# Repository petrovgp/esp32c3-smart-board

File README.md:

# ESP32-C3 Smart Board

A compact, battery-powered ESP32-C3 development board designed in **KiCad 9**, integrating power management, motion sensing, and display support in a small form factor. Ideal for low-power IoT or wearable applications.

## 🏢 Sponsor of today's project - PCBWay!

A huge thank you to PCBWay for sponsoring this project!

PCBWay provided high-quality PCB fabrication and assembly support, helping bring the hardware from prototype to reality. Their fast turnaround times, excellent communication, and reliable manufacturing made a big difference in the development process.

If you're looking for PCB manufacturing, assembly, CNC, or 3D-printing services, check out PCBWay **[here!](https://www.pcbway.com)**

Production files for this project were created using PCBWay KiCAD plugin and they can be used in PCBWay PCB and PCBA services right away!

Thanks again to PCBWay for supporting open-source hardware projects!

## 📸 Board design

---

## 🧠 Features

### ⚡ Core
- **ESP32-C3** RISC-V microcontroller with Wi-Fi and BLE 5.0
- Compact **42 × 45 mm** PCB designed in KiCad 9
  - 4 layer stackup: L1 Signal | L2 Ground | L3 Ground | L4 Signal + Power
- Integrated **Inverted-F antenna** for stable wireless performance

### 🔋 Power System
- Operable from **Li-Ion / Li-Po battery** and **USB Type C**
- On-board **TP4056** linear charging IC
  - 250mA charging current configuration
- **DW01A + FS8205A** dual MOSFET battery protection circuit
- Power-sharing design — board can operate **while charging**
- **ME6211C** LDO regulator:
  - 500 mA max output current
  - 100 mV dropout at 100 mA

### 🧭 Sensors
- **MPU6050** 6-axis accelerometer and gyroscope  
  - Interrupt pin connected to ESP32-C3 for motion wake-up or gesture detection

### 🖥️ Display
- **GC9A01** round TFT display connector
  - 12-pin FPC interface for bare display module

### 🔌 Connectivity
- **USB Type-C** connector for power and programming
- Exposed UART pins for debugging

## 🧩 Production files
All design files were created in **KiCad 9** and production files have been exported with **PCBWay plugin** (available **[here](https://github.com/pcbway/PCBWay-Plug-in-for-Kicad.git)**):
- `schematics/` – full circuit schematics
- `kicad/` – KiCAD 9 project files
- `kicad/production/` – ready-to-manufacture files (GERBERs + BOM)

Adjustment of production files might be needed. Please check carefully before placing any manufacturing orders.

## 🧾 Revisions

| Revision | Manufactured | Notes | Available |
|-----------|------|-------|-----------|
| **v1.0** | Nov 2025 | Improper GC9A01 footprint (wrong pitch), improper PMOS power sharing footprint (SOT23-5 instead of SOT23-3), everything else verified as OK  | Not available on Github
| **v1.1** | _Not manufactured_ | Updated GC9A01 footprint pitch, updated PMOS power sharing footprint, layout and silkscreen changes | Tagged v1.1 on Github
| **v1.2** | Dec 2025 | Layout and silkscreen changes | Tagged v1.2 on Github
| **v1.3** | _Not manufactured_ | Footprint changes, battery section layout changes, rounded antenna trace, bottom layer 3.3V plane addition, layout and silkscreen changes| Tagged v1.3 on Github

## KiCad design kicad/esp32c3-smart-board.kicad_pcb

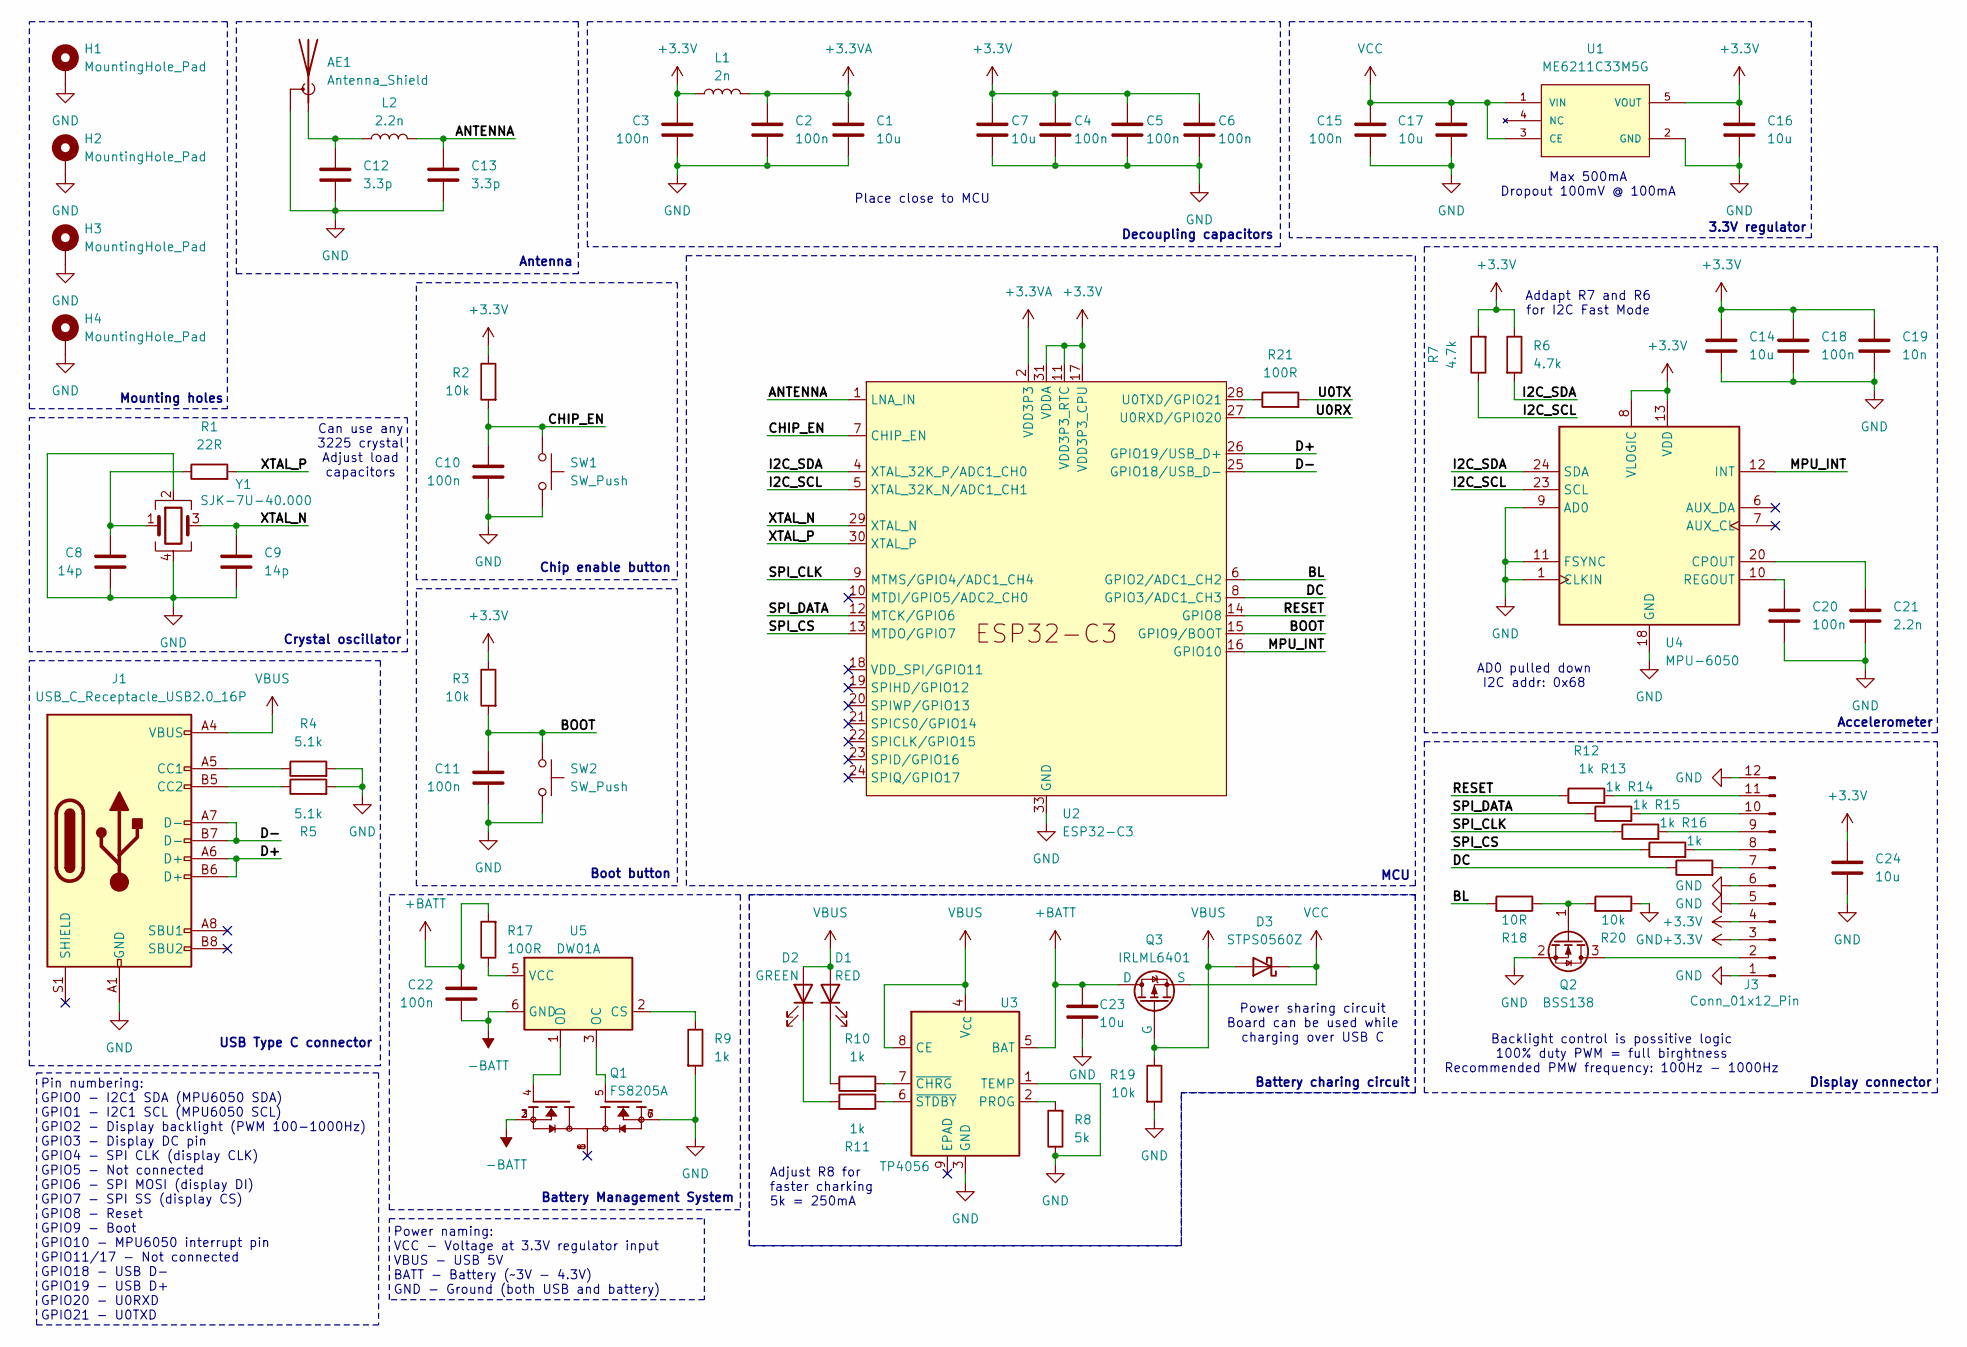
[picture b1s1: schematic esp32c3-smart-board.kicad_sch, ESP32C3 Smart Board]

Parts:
AE1: Antenna_Shield; Texas_SWRA117D_2.4GHz_Right
C1, C7, C14, C16, C17, C23, C24: 10u; C_0402_1005Metric
C2, C3, C4, C5, C6, C10, C11, C15, C18, C20, C22: 100n; C_0402_1005Metric
C8, C9: 14p; C_0402_1005Metric
C12, C13: 3.3p; C_0402_1005Metric
C19: 10n; C_0402_1005Metric
C21: 2.2n; C_0402_1005Metric
D1: RED; LED_0402_1005Metric
D2: GREEN; LED_0402_1005Metric
D3: STPS0560Z; D_SOD-123
H1, H2, H3, H4: MountingHole_Pad; MountingHole_2.2mm_M2_DIN965_Pad
J1: USB_C_Receptacle_USB2.0_16P; USB_C_Receptacle_GCT_USB4105-xx-A_16P_TopMnt_Horizontal
J3: Conn_01x12_Pin; GC9A01-12PIN-FPC
L1: 2n; L_0402_1005Metric
L2: 2.2n; L_0402_1005Metric
Q1: FS8205A; TSSOP-8_4.4x3mm_P0.65mm
Q2: BSS138; SOT-23-3
Q3: IRLML6401; SOT-23-3
R1: 22R; R_0402_1005Metric
R2, R3, R19, R20: 10k; R_0402_1005Metric
R4, R5: 5.1k; R_0402_1005Metric
R6, R7: 4.7k; R_0402_1005Metric
R8: 5k; R_0402_1005Metric
R9, R10, R11, R12, R13, R14, R15, R16: 1k; R_0402_1005Metric
R17, R21: 100R; R_0402_1005Metric
R18: 10R; R_0402_1005Metric
SW1, SW2: SW_Push; SW_Push_1P1T_NO_CK_KMR2
U1: ME6211C33M5G; SOT-23-5
U2: ESP32-C3; QFN-32-1EP_5x5mm_P0.5mm_EP3.45x3.45mm_ThermalVias
U3: TP4056; SOIC-8-1EP_3.9x4.9mm_P1.27mm_EP2.41x3.3mm_ThermalVias
U4: MPU-6050; InvenSense_QFN-24_4x4mm_P0.5mm
U5: DW01A; SOT-23-6
Y1: SJK-7U-40.000; Crystal_SMD_3225-4Pin_3.2x2.5mm

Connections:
+3.3V: C3.1, C4.1, C5.1, C6.1, C7.1, C14.1, C16.1, C18.1, C19.1, C24.1, J3.3, J3.4, L1.1, R2.1, R3.1, R6.1, R7.2, U1.5 (VOUT), U2.11 (VDD3P3_RTC), U2.17 (VDD3P3_CPU), U2.31 (VDDA), U2.32 (VDDA), U4.8 (VLOGIC), U4.13 (VDD)
+3.3VA: C1.1, C2.1, L1.2, U2.2 (VDD3P3), U2.3 (VDD3P3)
+BATT: C22.1, C23.1, Q3.1 (D), R17.2, U3.5 (BAT)
-BATT: C22.2, Q1.2, Q1.3, U5.6 (GND)
/ANTENNA: C13.1, L2.1, U2.1 (LNA_IN)
/BL: R18.2, U2.6 (GPIO2/ADC1_CH2)
/BOOT: C11.1, R3.2, SW2.1, U2.15 (GPIO9/BOOT)
/CHIP_EN: C10.1, R2.2, SW1.1, U2.7 (CHIP_EN)
/D+: J1.A6 (D+), J1.B6 (D+), U2.26 (GPIO19/USB_D+)
/D-: J1.A7 (D-), J1.B7 (D-), U2.25 (GPIO18/USB_D-)
/DC: R16.1, U2.8 (GPIO3/ADC1_CH3)
/I2C_SCL: R7.1, U2.5 (XTAL_32K_N/ADC1_CH1), U4.23 (SCL)
/I2C_SDA: R6.2, U2.4 (XTAL_32K_P/ADC1_CH0), U4.24 (SDA)
/MPU_INT: U2.16 (GPIO10), U4.12 (INT)
/RESET: R12.1, U2.14 (GPIO8)
/SPI_CLK: R14.1, U2.9 (MTMS/GPIO4/ADC1_CH4)
/SPI_CS: R15.1, U2.13 (MTDO/GPIO7)
/SPI_DATA: R13.1, U2.12 (MTCK/GPIO6)
/U0RX: U2.27 (U0RXD/GPIO20)
/U0TX: R21.2
/XTAL_N: C9.1, U2.29 (XTAL_N), Y1.3
/XTAL_P: R1.2, U2.30 (XTAL_P)
GND: AE1.2 (Shield), C1.2, C2.2, C3.2, C4.2, C5.2, C6.2, C7.2, C8.2, C9.2, C10.2, C11.2, C12.2, C13.2, C14.2, C15.2, C16.2, C17.2, C18.2, C19.2, C20.2, C21.2, C23.2, C24.2, H1.1, H2.1, H3.1, H4.1, J1.A1 (GND), J1.A12 (GND), J1.B1 (GND), J1.B12 (GND), J3.1, J3.5, J3.6, J3.12, Q1.6, Q1.7, Q2.2 (S), R4.2, R5.2, R8.1, R9.2, R19.2, R20.1, SW1.2, SW2.2, U1.2 (GND), U2.33 (GND), U3.1 (TEMP), U3.3 (GND), U4.1 (CLKIN), U4.9 (AD0), U4.11 (FSYNC), U4.18 (GND), Y1.2, Y1.4
unnamed: AE1.1 (A), C12.1, L2.2
unnamed: C8.1, R1.1, Y1.1
unnamed: D1.1 (K), R10.1
unnamed: D2.1 (K), R11.2
unnamed: J1.A5 (CC1), R4.1
unnamed: J1.B5 (CC2), R5.1
unnamed: J3.2, Q2.3 (D)
unnamed: J3.7, R16.2
unnamed: J3.8, R15.2
unnamed: J3.9, R14.2
unnamed: J3.10, R13.2
unnamed: J3.11, R12.2
unnamed: Q2.1 (G), R18.1, R20.2
unnamed: R21.1, U2.28 (U0TXD/GPIO21)
unnamed: R8.2, U3.2 (PROG)
unnamed: R10.2, U3.7 (~CHRG)
unnamed: R11.1, U3.6 (~STDBY)
unnamed: C21.1, U4.20 (CPOUT)
unnamed: C20.1, U4.10 (REGOUT)
unnamed: R9.1, U5.2 (CS)
unnamed: Q1.5, U5.3 (OC)
unnamed: Q1.4, U5.1 (OD)
unnamed: R17.1, U5.5 (VCC)
VBUS: D1.2 (A), D2.2 (A), D3.2 (A), J1.A4 (VBUS), J1.A9 (VBUS), J1.B4 (VBUS), J1.B9 (VBUS), Q3.2 (G), R19.1, U3.4 (V_{CC}), U3.8 (CE)
VCC: C15.1, C17.1, D3.1 (K), Q3.3 (S), U1.1 (VIN), U1.3 (CE)

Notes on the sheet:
Display connector
Antenna
Chip enable button
Addapt R7 and R6 for I2C Fast Mode
Decoupling capacitors
Can use any 3225 crystal Adjust load capacitors
Mounting holes
Battery charing circuit
USB Type C connector
Battery Management System
Adjust R8 for faster charking 5k = 250mA
Power sharing circuit Board can be used while charging over USB C
Max 500mA Dropout 100mV @ 100mA
Accelerometer
Place close to MCU
AD0 pulled down I2C addr: 0x68
Pin numbering: GPIO0 - I2C1 SDA (MPU6050 SDA) GPIO1 - I2C1 SCL (MPU6050 SCL) GPIO2 - Display backlight (PWM 100-1000Hz) GPIO3 - Display DC pin GPIO4 - SPI CLK (display CLK) GPIO5 - Not connected GPIO6 - SPI MOSI (display DI) GPIO7 - SPI SS (display CS) GPIO8 - Reset GPIO9 - Boot GPIO10 - MPU6050 in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
Boot button
Power naming: VCC - Voltage at 3.3V regulator input VBUS - USB 5V BATT - Battery (~3V - 4.3V) GND - Ground (both USB and battery)
Crystal oscillator
MCU
3.3V regulator
Backlight control is possitive logic 100% duty PWM = full birghtness Recommended PMW frequency: 100Hz - 1000Hz

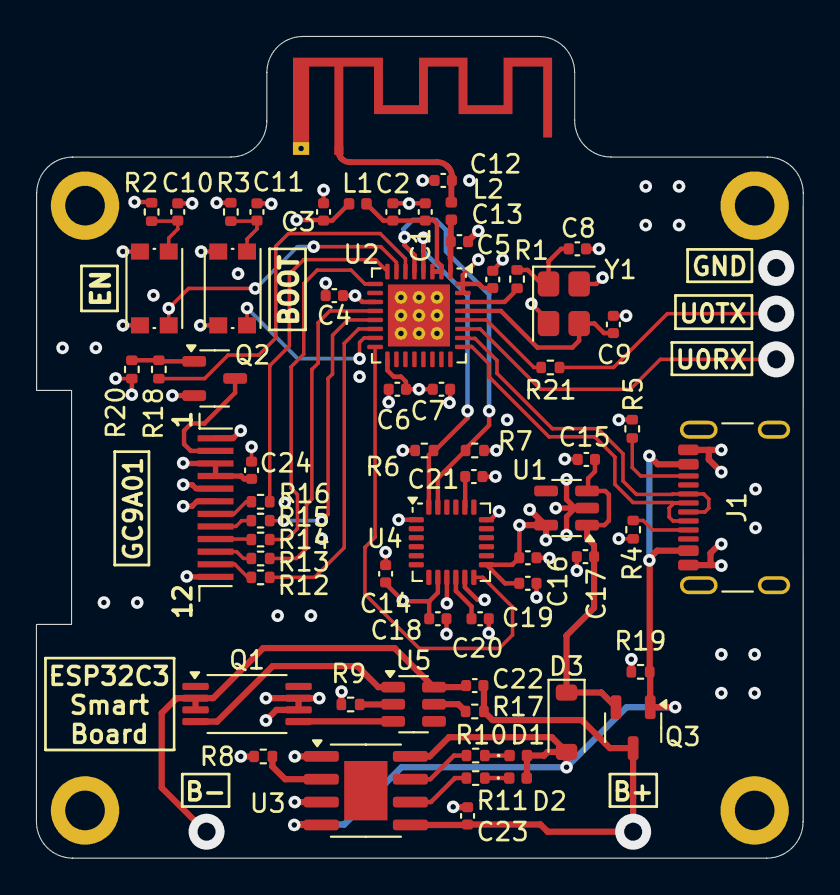
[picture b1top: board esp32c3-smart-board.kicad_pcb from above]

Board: 4 copper layers, 42.6 x 45.7 mm, 68 parts (0 on the bottom side), 46 nets.

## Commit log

2025-11-09 Add schematic
2025-11-09 Add KiCAD 9 project and production files
2025-11-09 Add board design images
2025-11-10 Add revisions to README.md and revision 1 production image
2025-11-16 Update KiCAD project files
2025-11-16 Update production files
2025-11-16 Update board design images
2025-11-30 Update images from manufactured board
2025-11-30 Add sponsor section in README.md
2025-11-30 Fix typo in sponsor section of README
2025-12-05 Add board layer stackup to README.md
2025-12-26 Initial datasheet document
